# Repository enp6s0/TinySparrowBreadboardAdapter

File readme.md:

# TinySparrow breadboard adapter

Quick and dirty adapter for when you really need [TinySparrow](https://github.com/enp6s0/TinySparrow) on a breadboard. This
adapter makes for an easier prototyping experience, transforming TinySparrow into something that can be plugged directly
to a breadboard with 2x 16-pin 2.54mm headers with the same spacing as an Arduino Nano.

Board also provides nice breakout connectors for SWD programming/debug (5-pin 2.54mm) and a tap for the CAN bus (3-pin Phoenix 3.81mm)

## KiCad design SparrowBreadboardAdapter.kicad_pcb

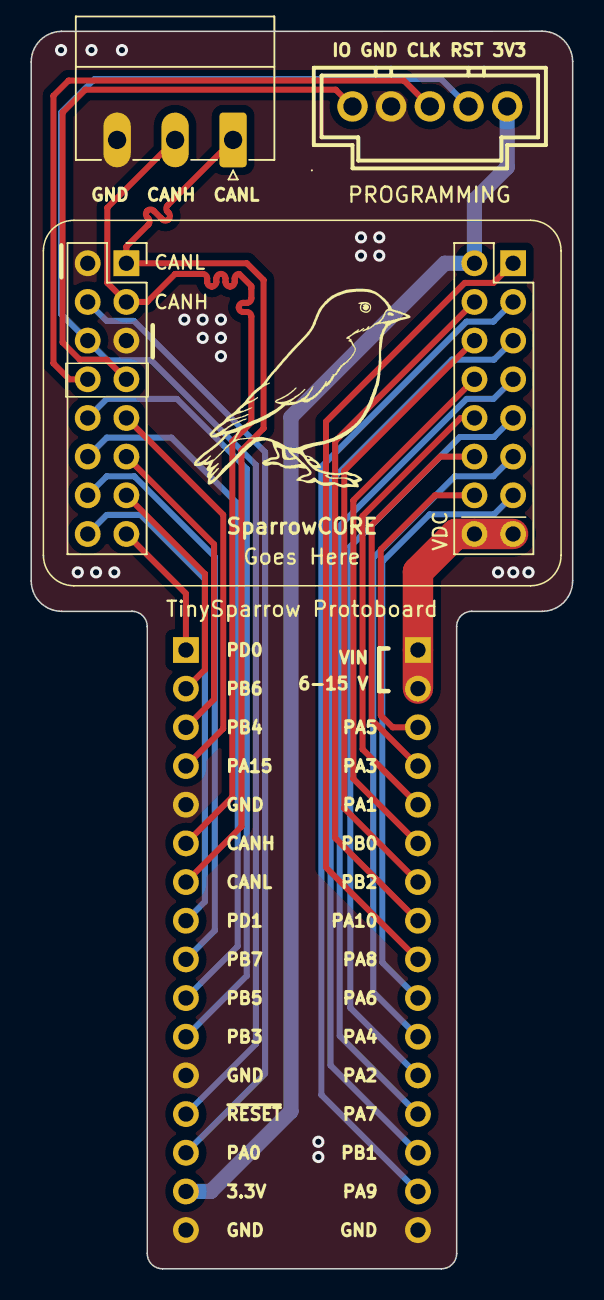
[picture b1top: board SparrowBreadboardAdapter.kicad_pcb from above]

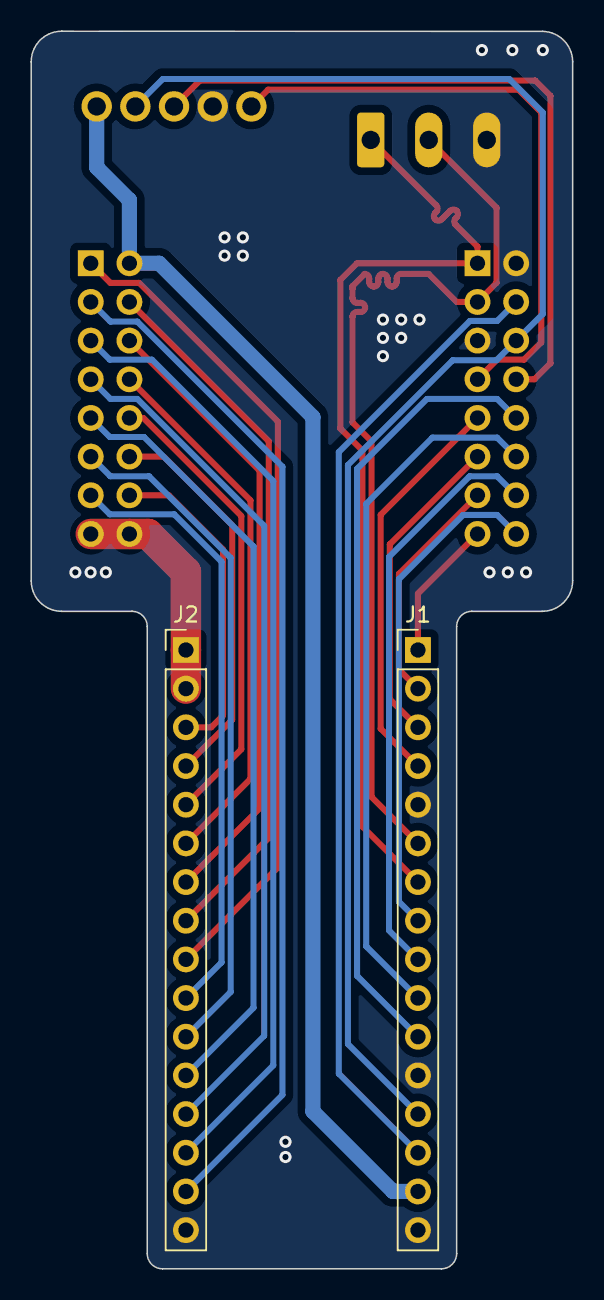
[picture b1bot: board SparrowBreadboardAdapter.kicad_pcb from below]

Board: 2 copper layers, 35.6 x 81.3 mm, 5 parts (2 on the bottom side), 30 nets.

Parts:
J1: LEFT_SIDE_CONN; PinHeader_1x16_P2.54mm_Vertical
J2: RIGHT_SIDE_CONN; PinHeader_1x16_P2.54mm_Vertical
J3: CAN_DEBUG; PhoenixContact_MC_1,5_3-G-3.81_1x03_P3.81mm_Horizontal
J4: SYS_PROG; CONN-TH_A2547WV-5P
U1: SparrowCore

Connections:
+3V3: J1.15, J4.5, U1.18 (3V_OUT)
/CAN+: J1.6, J3.2, U1.3 (CANH)
/CAN-: J1.7, J3.1, U1.1 (CANL)
/PA0: J1.14, U1.4 (PA0)
/PA1: J2.5, U1.26 (PA1)
/PA2: J2.12, U1.25 (PA2)
/PA3: J2.4, U1.28 (PA3)
/PA4: J2.11, U1.27 (PA4)
/PA5: J2.3, U1.30 (PA5)
/PA6: J2.10, U1.29 (PA6)
/PA7: J2.13, U1.23 (PA7)
/PA8: J2.9, U1.17 (PA8)
/PA9: J2.15, U1.19 (PA9)
/PA10: J2.8, U1.20 (PA10)
/PA15: J1.4, U1.9 (PA15)
/PB0: J2.6, U1.24 (PB0)
/PB1: J2.14, U1.21 (PB1)
/PB2: J2.7, U1.22 (PB2)
/PB3: J1.11, U1.10 (PB3)
/PB4: J1.3, U1.11 (PB4)
/PB5: J1.10, U1.12 (PB5)
/PB6: J1.2, U1.13 (PB6)
/PB7: J1.9, U1.14 (PB7)
/PD0: J1.1, U1.15 (PD0)
/PD1: J1.8, U1.16 (PD1)
/SWCLK: J4.3, U1.8 (SWCLK)
/SWDIO: J4.1, U1.7 (SWDIO)
/VDC: J2.1, J2.2, U1.31 (VDC), U1.32 (VDC)
/~RESET: J1.13, J4.4, U1.6 (~RESET)
GND: J1.5, J1.12, J1.16, J2.16, J3.3, J4.2, U1.2 (GND), U1.5 (GND)

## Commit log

2024-02-23 Initial push
